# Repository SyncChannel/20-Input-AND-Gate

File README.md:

# 20-Input-AND-Gate
https://oshpark.com/shared_projects/KGzFkPWY

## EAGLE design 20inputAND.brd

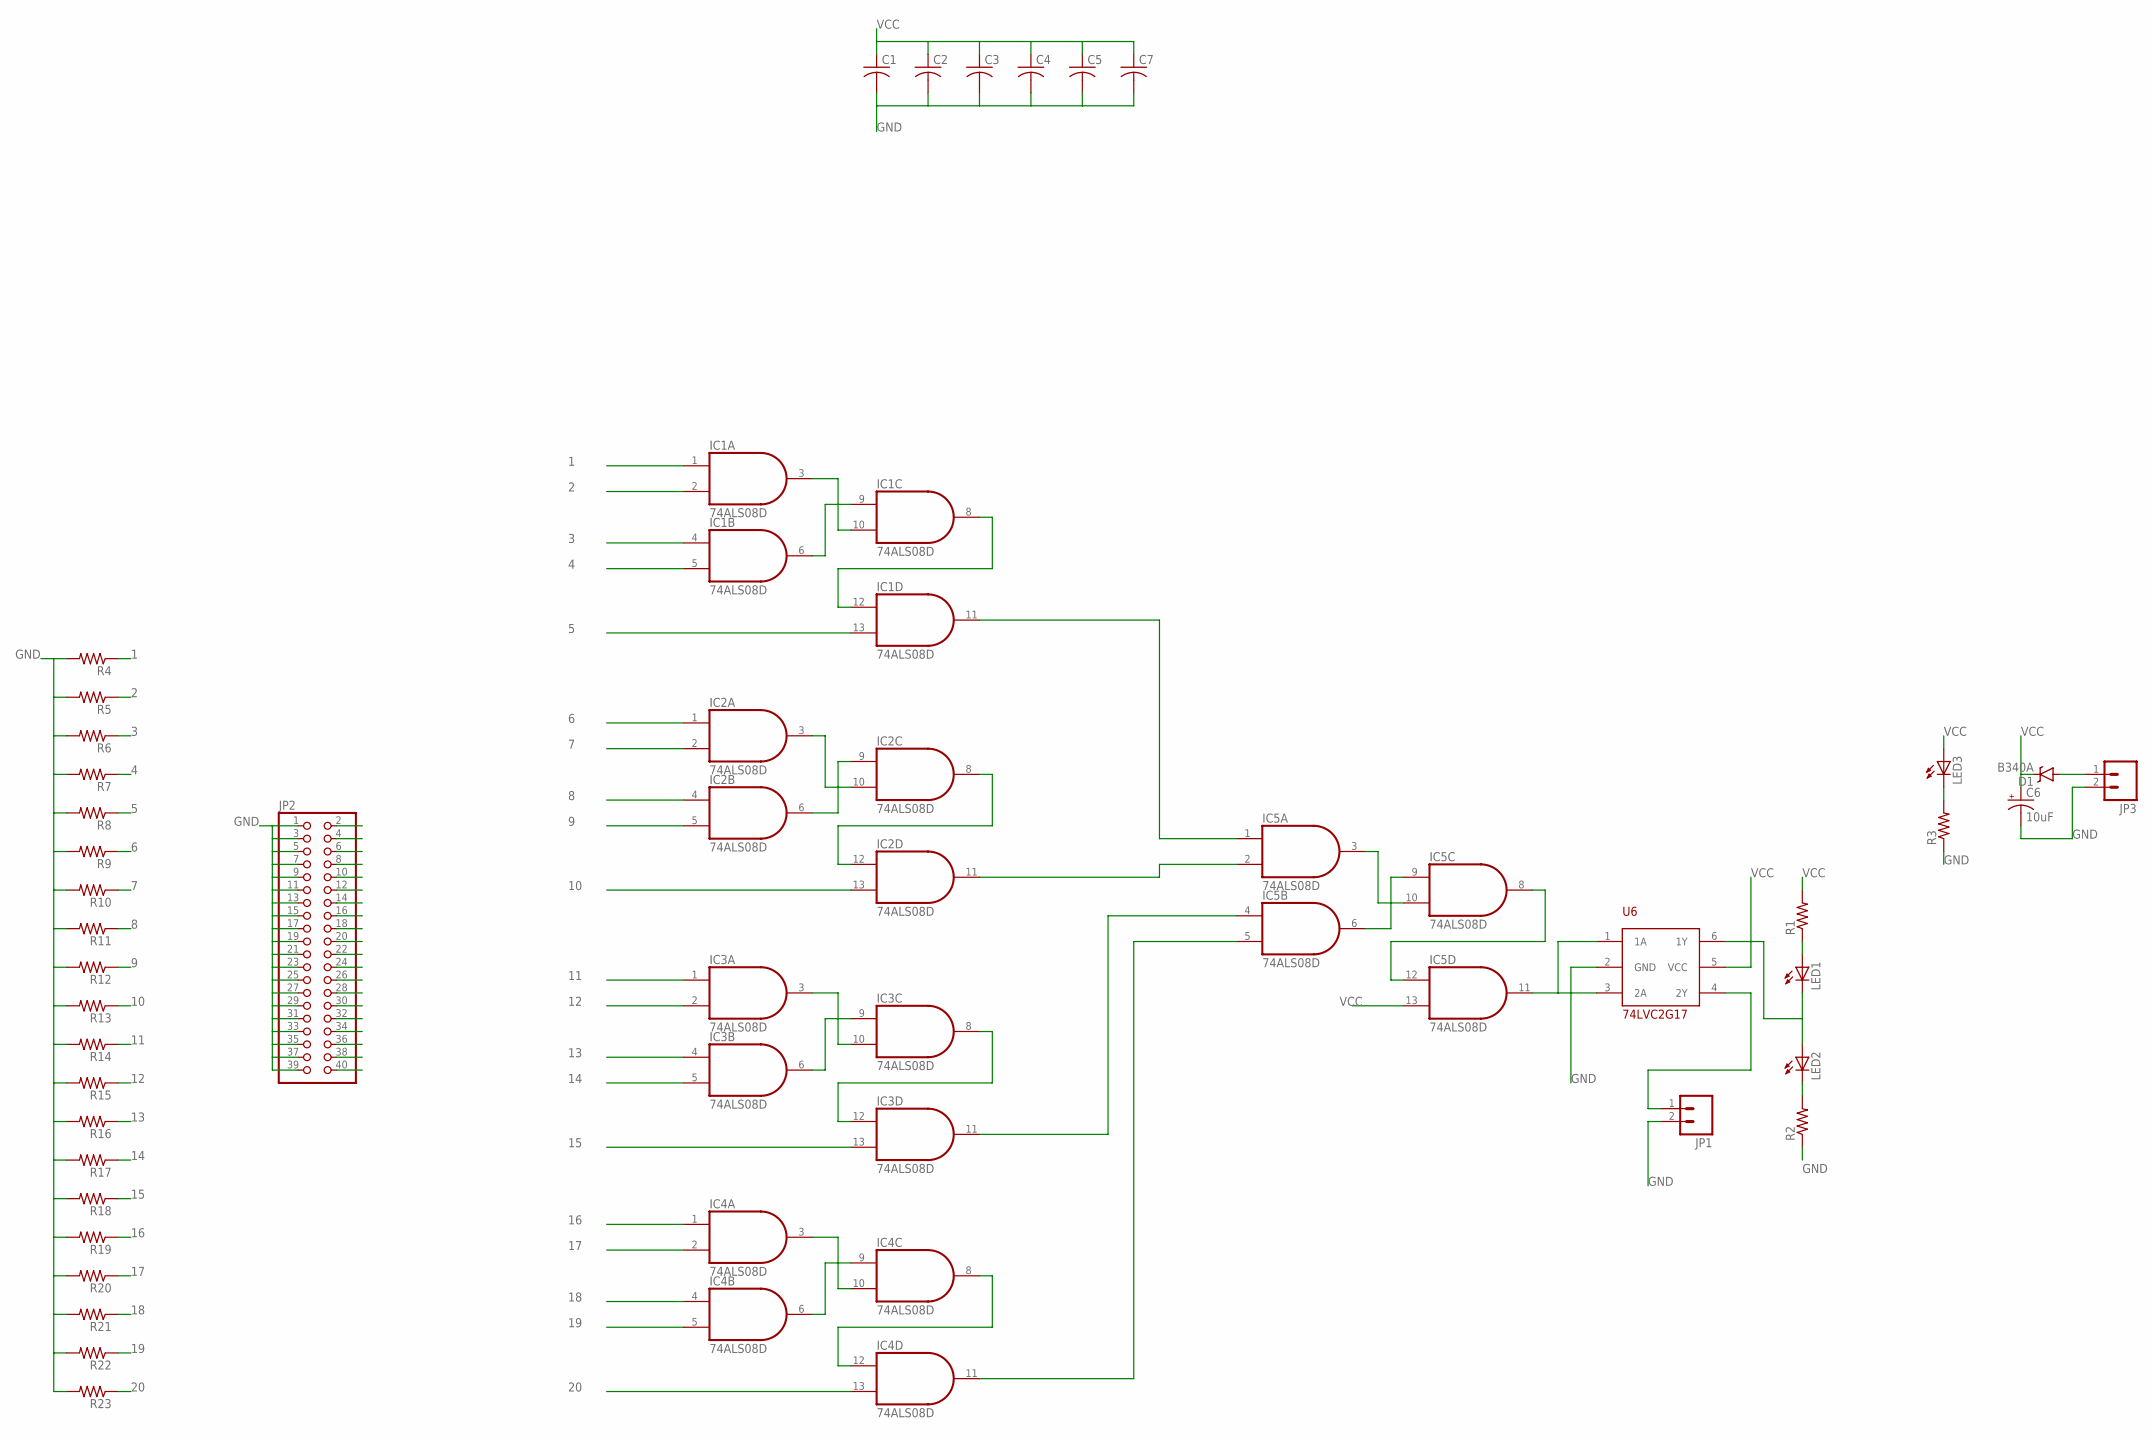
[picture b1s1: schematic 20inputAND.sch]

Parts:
C1, C2, C3, C4, C5, C7: C-USC0603; C0603
C6: 10uF; EIA3216
D1: B340A; SMA-DIODE
IC1, IC2, IC3, IC4, IC5: 74ALS08D; SO14
JP1, JP3: M02PTH; 1X02
JP2: PINHD-2X20; 2X20
LED1, LED2: LEDCHIPLED_1206; CHIPLED_1206
LED3: LEDCHIPLED_0805; CHIPLED_0805
R1, R2, R3, R4, R5, R6, R7, R8, R9, R10, R11, R12, R13, R14, R15, R16, R17, R18, R19, R20, R21, R22, R23: R-US_R0603; R0603
U$2: 74LVC2G14/7; SOT23-6

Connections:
1: IC1.1 (I0), JP2.2, R4.1
2: IC1.2 (I1), JP2.4, R5.1
3: IC1.4 (I0), JP2.6, R6.1
4: IC1.5 (I1), JP2.8, R7.1
5: IC1.13 (I1), JP2.10, R8.1
6: IC2.1 (I0), JP2.12, R9.1
7: IC2.2 (I1), JP2.14, R10.1
8: IC2.4 (I0), JP2.16, R11.1
9: IC2.5 (I1), JP2.18, R12.1
10: IC2.13 (I1), JP2.20, R13.1
11: IC3.1 (I0), JP2.22, R14.1
12: IC3.2 (I1), JP2.24, R15.1
13: IC3.4 (I0), JP2.26, R16.1
14: IC3.5 (I1), JP2.28, R17.1
15: IC3.13 (I1), JP2.30, R18.1
16: IC4.1 (I0), JP2.32, R19.1
17: IC4.2 (I1), JP2.34, R20.1
18: IC4.4 (I0), JP2.36, R21.1
19: IC4.5 (I1), JP2.38, R22.1
20: IC4.13 (I1), JP2.40, R23.1
GND: C1.2, C2.2, C3.2, C4.2, C5.2, C6.C (-), C7.2, IC1.7 (GND), IC2.7 (GND), IC3.7 (GND), IC4.7 (GND), IC5.7 (GND), JP1.2, JP2.1, JP2.3, JP2.5, JP2.7, JP2.9, JP2.11, JP2.13, JP2.15, JP2.17, JP2.19, JP2.21, JP2.23, JP2.25, JP2.27, JP2.29, JP2.31, JP2.33, JP2.35, JP2.37, JP2.39, JP3.2, R2.1, R3.1, R4.2, R5.2, R6.2, R7.2, R8.2, R9.2, R10.2, R11.2, R12.2, R13.2, R14.2, R15.2, R16.2, R17.2, R18.2, R19.2, R20.2, R21.2, R22.2, R23.2, U$2.2 (GND)
unnamed: LED1.A, R1.1
unnamed: D1.A, JP3.1
unnamed: LED2.C, R2.2
unnamed: IC1.6 (O), IC1.9 (I0)
unnamed: IC1.3 (O), IC1.10 (I1)
unnamed: IC1.8 (O), IC1.12 (I0)
unnamed: LED3.C, R3.2
unnamed: IC1.11 (O), IC5.1 (I0)
unnamed: IC2.3 (O), IC2.10 (I1)
unnamed: IC2.6 (O), IC2.9 (I0)
unnamed: IC3.6 (O), IC3.9 (I0)
unnamed: IC3.3 (O), IC3.10 (I1)
unnamed: IC2.8 (O), IC2.12 (I0)
unnamed: IC4.6 (O), IC4.9 (I0)
unnamed: IC4.3 (O), IC4.10 (I1)
unnamed: IC2.11 (O), IC5.2 (I1)
unnamed: IC5.6 (O), IC5.9 (I0)
unnamed: IC5.3 (O), IC5.10 (I1)
unnamed: LED1.C, LED2.A, U$2.6 (1Y)
unnamed: IC5.11 (O), U$2.1 (1A), U$2.3 (2A)
unnamed: IC3.8 (O), IC3.12 (I0)
unnamed: JP1.1, U$2.4 (2Y)
unnamed: IC3.11 (O), IC5.4 (I0)
unnamed: IC4.8 (O), IC4.12 (I0)
unnamed: IC4.11 (O), IC5.5 (I1)
unnamed: IC5.8 (O), IC5.12 (I0)
VCC: C1.1, C2.1, C3.1, C4.1, C5.1, C6.A (+), C7.1, D1.C, IC1.14 (VCC), IC2.14 (VCC), IC3.14 (VCC), IC4.14 (VCC), IC5.13 (I1), IC5.14 (VCC), LED3.A, R1.2, U$2.5 (VCC)

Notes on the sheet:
74LVC2G17

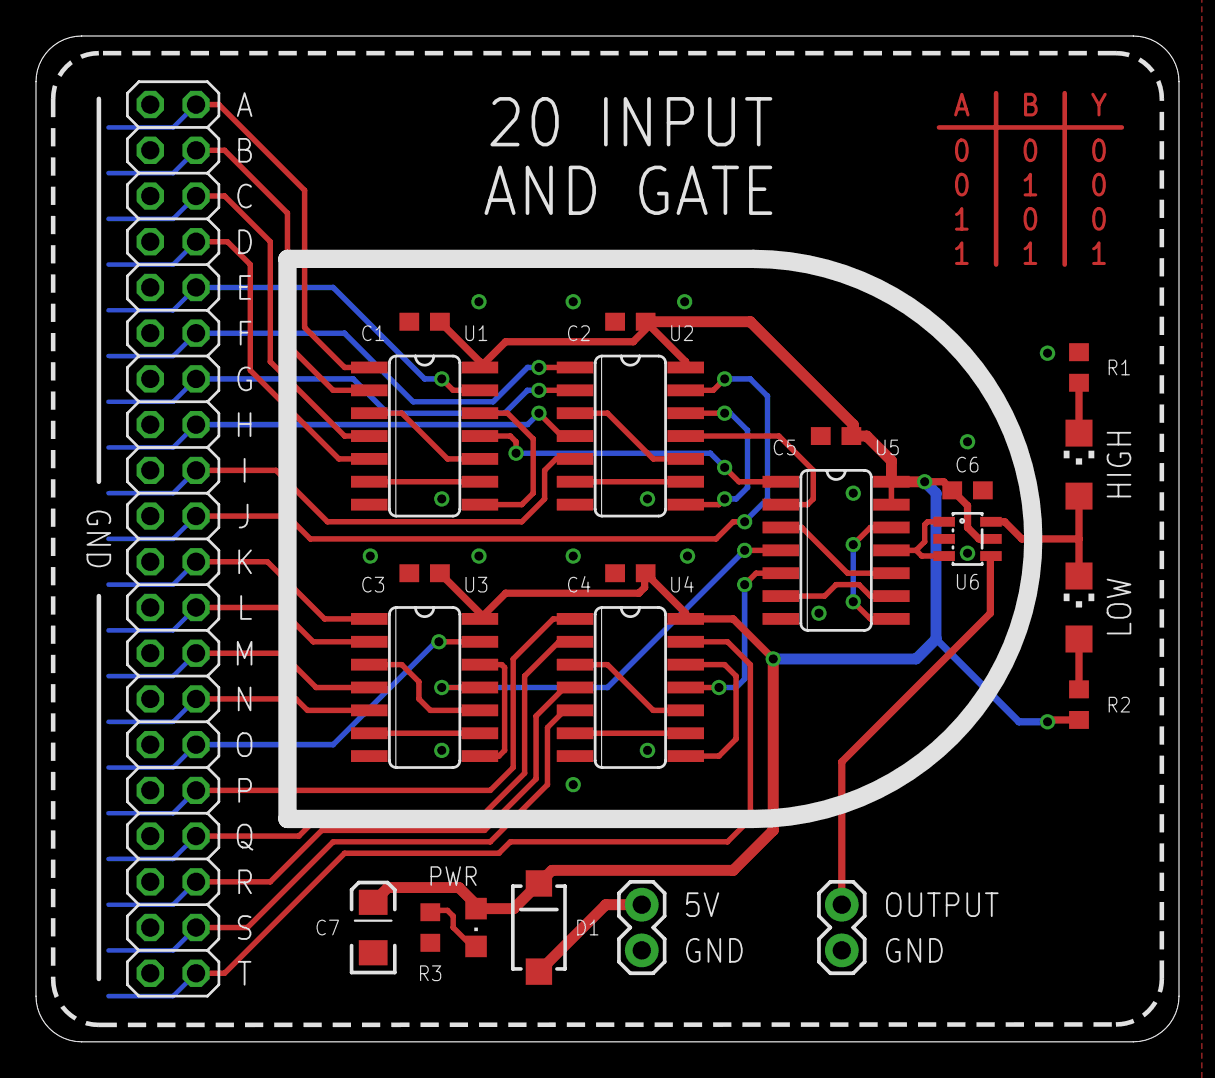
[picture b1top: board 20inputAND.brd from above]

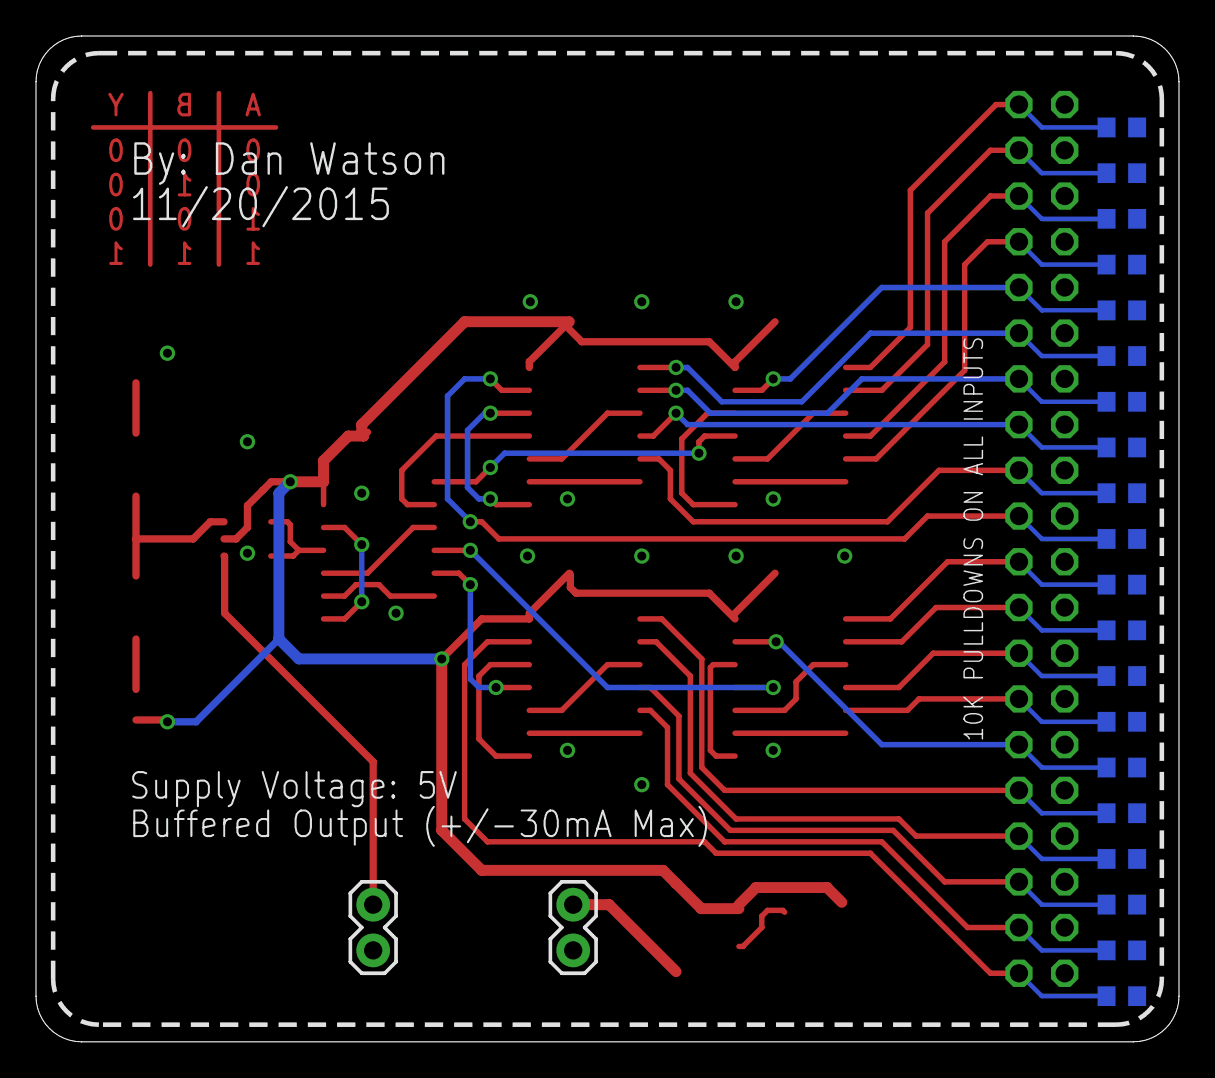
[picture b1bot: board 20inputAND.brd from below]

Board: 2 copper layers, 63.5 x 55.9 mm, 43 parts (20 on the bottom side), 48 nets.

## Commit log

2017-09-16 Update LICENSE
    The hardware and software source files contained in this library are released under the Creative Commons ShareAlike 4.0 International license: https://creativecommons.org/licenses/by-sa/4.0/
2017-09-23 Update LICENSE

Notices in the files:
parts and their libraries:
SparkFun-Connectors: Licensing: Creative Commons ShareAlike 4.0 International - https://creativecommons.org/licenses/by-sa/4.0
